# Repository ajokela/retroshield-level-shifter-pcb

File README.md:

# RetroShield Level Shifter PCB — Arduino Giga R1 Shield

KiCad design files for a bidirectional 3.3V-to-5V level converter shield that sits between an [Arduino Giga R1 WiFi](https://store.arduino.cc/products/giga-r1-wifi) and a [RetroShield Z80](https://www.tindie.com/products/8bitforce/retroshield-for-arduino-mega-z80/). The shield translates all bus signals between the Giga's 3.3V logic and the RetroShield's 5V logic.

## Design Overview

**Version:** V0.2

V0.1 used nine identical TXB0108PW auto-direction-sensing level translators. In practice, the TXB0108's direction sensing failed for several Z80 bus signals: `IORQ_N` and `RD_N` were stuck HIGH, the data bus was invisible during IO writes, and `WR_N` was unreliable during IO cycles. The firmware worked around these failures with ~1,300 lines of shadow register tracking code.

V0.2 replaces 5 of the 9 TXB0108s with purpose-matched ICs that have explicit direction control, eliminating these failures entirely:

| Position | IC | Package | Role |
|----------|---|---------|------|
| U1, U2, U3 | **SN74LVC541** | TSSOP-20 | Address bus + control inputs (5V→3.3V) |
| U4 | **SN74AHCT541** | TSSOP-20 | Control outputs (3.3V→5V) |
| U5 | **SN74LVC4245A** | TSSOP-24 | Data bus (bidirectional, explicit DIR) |
| U6–U9 | TXB0108PW | TSSOP-20 | Pass-through GPIO (unchanged) |

**Board specifications:**
- **Dimensions:** 155mm x 90mm (matches Arduino Giga R1 footprint)
- **Layers:** 2-layer PCB
- **Signals translated:** 72 channels covering data bus, address bus, and control signals
- **DIR pin:** Arduino D2 → U5 pin 2 (controls data bus direction)

### Signal Groups

| Signal Group | Pins | Channels | Direction | IC |
|-------------|------|----------|-----------|-----|
| Address bus A0–A7 | D22–D29 | 8 | Z80 → Arduino (5V→3.3V) | U1 (74LVC541) |
| Address bus A8–A15 | D30–D37 | 8 | Z80 → Arduino (5V→3.3V) | U2 (74LVC541) |
| Control (MREQ, IORQ, RD, WR) | D39–D41, D53 | 4 | Z80 → Arduino (5V→3.3V) | U3 (74LVC541) |
| Control (CLK, RESET, INT, NMI) | D38, D50–D52 | 4 | Arduino → Z80 (3.3V→5V) | U4 (74AHCT541) |
| Data bus D0–D7 | D42–D49 | 8 | Bidirectional (DIR pin) | U5 (SN74LVC4245A) |
| Remaining GPIO | Various | 40 | Bidirectional (auto-sense) | U6–U9 (TXB0108) |

### IC Selection Rationale

- **74LVC541** (U1–U3): VCC=3.3V, inputs are 5V-tolerant. Unidirectional buffer — no direction sensing ambiguity. OE pins tied to GND (always enabled). No pull-up resistors needed.
- **74AHCT541** (U4): VCC=5V, TTL-compatible inputs accept 3.3V drive levels. Unidirectional buffer for Arduino→Z80 control signals. OE pins tied to GND.
- **SN74LVC4245A** (U5): VCCA=3.3V, VCCB=5V. Bidirectional transceiver with explicit DIR pin. DIR HIGH = A→B (Giga drives Z80 data bus), DIR LOW = B→A (Z80 drives Giga). OE tied to GND. DIR pin connected directly to Arduino D2 at 3.3V (does not go through a level shifter).
- **TXB0108PW** (U6–U9): Retained for pass-through GPIO where auto-direction sensing works fine. OE pins pulled HIGH via 10K resistors to 3.3V.

### DIR Pin

The SN74LVC4245A (U5) requires one GPIO from the Giga for direction control:

- **Arduino pin D2** (directly connected at 3.3V, no level shifter)
- **DIR HIGH** → A→B: Giga drives Z80 data bus (memory/IO writes to Z80)
- **DIR LOW** → B→A: Z80 drives Giga data bus (memory/IO reads from Z80)

This single GPIO wire replaces the entire shadow register architecture from v0.1.

## Repository Contents

```
kicad/                  KiCad 8 source files
  ├── AlexJ_bz_ArduinoGigaShield.kicad_pro    Project file
  ├── AlexJ_bz_ArduinoGigaShield.kicad_sch    Schematic
  ├── AlexJ_bz_ArduinoGigaShield.kicad_pcb    PCB layout
  └── AlexJ_bz_ArduinoGigaShield.kicad_prl    Project preferences

gerber/                 Production-ready Gerber files (v0.1 — regenerate from KiCad for v0.2)
  ├── *-F_Cu.gbr           Front copper
  ├── *-B_Cu.gbr           Back copper
  ├── *-F_Mask.gbr         Front solder mask
  ├── *-B_Mask.gbr         Back solder mask
  ├── *-F_Silkscreen.gbr   Front silkscreen
  ├── *-B_Silkscreen.gbr   Back silkscreen
  ├── *-F_Paste.gbr        Front paste (for stencil)
  ├── *-B_Paste.gbr        Back paste
  ├── *-Edge_Cuts.gbr      Board outline
  ├── *-PTH.drl            Plated through-hole drill
  ├── *-NPTH.drl           Non-plated through-hole drill
  └── *-job.gbrjob         Gerber job file

bom/                    Bill of Materials
  ├── AlexJ_bz_ArduinoGigaShield.csv     CSV format
  └── AlexJ_bz_ArduinoGigaShield.xlsx    Excel format (v0.1)

cpl/                    Component Placement
  └── AlexJ_bz_ArduinoGigaShield-all-pos.csv   Pick & place positions

schematic/              Schematic PDF (v0.1 — regenerate from KiCad for v0.2)
  └── AlexJ_bz_ArduinoGigaShield.pdf

images/                 3D renders
  ├── AlexJ_bz_ArduinoGigaShield_TOP.jpg       Top view
  ├── AlexJ_bz_ArduinoGigaShield_TOP.png       Top view (PNG)
  ├── AlexJ_bz_ArduinoGigaShield_BTM.jpg       Bottom view
  └── AlexJ_bz_ArduinoGigaShield.png           Perspective view

CHANGES-V0.2.md         Detailed design changes for KiCad implementation
```

## Bill of Materials

| Reference | Qty | Value | Part Number | Package |
|-----------|-----|-------|-------------|---------|
| U1, U2, U3 | 3 | SN74LVC541 | SN74LVC541PWR | TSSOP-20 |
| U4 | 1 | SN74AHCT541 | SN74AHCT541PWR | TSSOP-20 |
| U5 | 1 | SN74LVC4245A | SN74LVC4245APWR | TSSOP-24 |
| U6–U9 | 4 | TXB0108PW | TXB0108PWR | TSSOP-20 |
| C1–C18 | 18 | 0.1 uF | CC0603KRX7R9BB104 | 0603 |
| R6–R9 | 4 | 10K | RC0603FR-0710KL | 0603 |

**Cap breakdown:** U1–U3 get 1 cap each (VCC only, single supply), U4 gets 1 cap (VCC only), U5 gets 2 caps (VCCA + VCCB), U6–U9 get 3 caps each (VCCA + VCCB + extra) = 3 + 1 + 2 + 12 = 18 caps.

**Resistors:** R6–R9 are 10K pull-ups on OE pins for U6–U9 (TXB0108). R1–R5 from v0.1 are removed — the 74LVC541, 74AHCT541, and SN74LVC4245A have their OE pins tied directly to GND.

## Manufacturing

The Gerber files in `gerber/` are from v0.1. After the KiCad schematic and PCB are updated for v0.2, regenerate Gerbers before ordering.

Upload to any PCB fabrication service:

- [PCBWay](https://www.pcbway.com/)
- [JLCPCB](https://jlcpcb.com/)
- [OSH Park](https://oshpark.com/)

For SMD assembly, provide the BOM (`bom/`) and component placement file (`cpl/`) to the fab house.

### Recommended PCB Specs

| Parameter | Value |
|-----------|-------|
| Layers | 2 |
| Board thickness | 1.6 mm |
| Copper weight | 1 oz |
| Surface finish | HASL or ENIG |
| Solder mask | Red (or your preference) |
| Silkscreen | White |

## Assembly Notes

1. **SMD components first** — solder the ICs, decoupling capacitors, and pull-up resistors
2. **Pin headers last** — solder the through-hole pin headers (female on bottom for the Giga, male on top for the RetroShield)
3. **Power jumper** — a jumper wire connects the Giga's 3.3V output to the shield's VCCA rail
4. **DIR wire** — connect Arduino D2 to U5 pin 2 (DIR) if not routed on the PCB
5. **Orientation** — check silkscreen for "V0.2" and IC labels; U5 is the wider TSSOP-24 package

## Photos

## Related Projects

- [retroshield-z80-cpm-giga](https://github.com/ajokela/retroshield-z80-cpm-giga) — Arduino Giga R1 firmware for CP/M 2.2 on the RetroShield Z80
- [retroshield-sector-server](https://github.com/ajokela/retroshield-sector-server) — Rust TCP server for WiFi-based CP/M disk I/O

## Blog Posts

This project is documented in a three-part series on [tinycomputers.io](https://tinycomputers.io):

1. [My Experience Using Fiverr for Custom PCB Design: A $468 Arduino Giga Shield](https://tinycomputers.io/posts/fiverr-pcb-design-arduino-giga-shield/)
2. [Porting CP/M to the Arduino Giga R1: When Level Converters Fight Back](https://tinycomputers.io/posts/cpm-on-arduino-giga-r1-wifi/)
3. [Playing Zork on a Real Z80: From CP/M Boot to the Great Underground Empire](https://tinycomputers.io/posts/zork-on-retroshield-z80-arduino-giga/)

## License

This work is licensed under the [Creative Commons Attribution-ShareAlike 4.0 International License](https://creativecommons.org/licenses/by-sa/4.0/) (CC BY-SA 4.0). See [LICENSE](LICENSE).

You are free to share and adapt this design, including for commercial purposes, as long as you give appropriate credit and distribute derivative works under the same license.

## Author

Alex Jokela — [tinycomputers.io](https://tinycomputers.io)

PCB design by Elijah (ekeziah) via Fiverr. Manufacturing sponsored by [PCBWay](https://www.pcbway.com/).

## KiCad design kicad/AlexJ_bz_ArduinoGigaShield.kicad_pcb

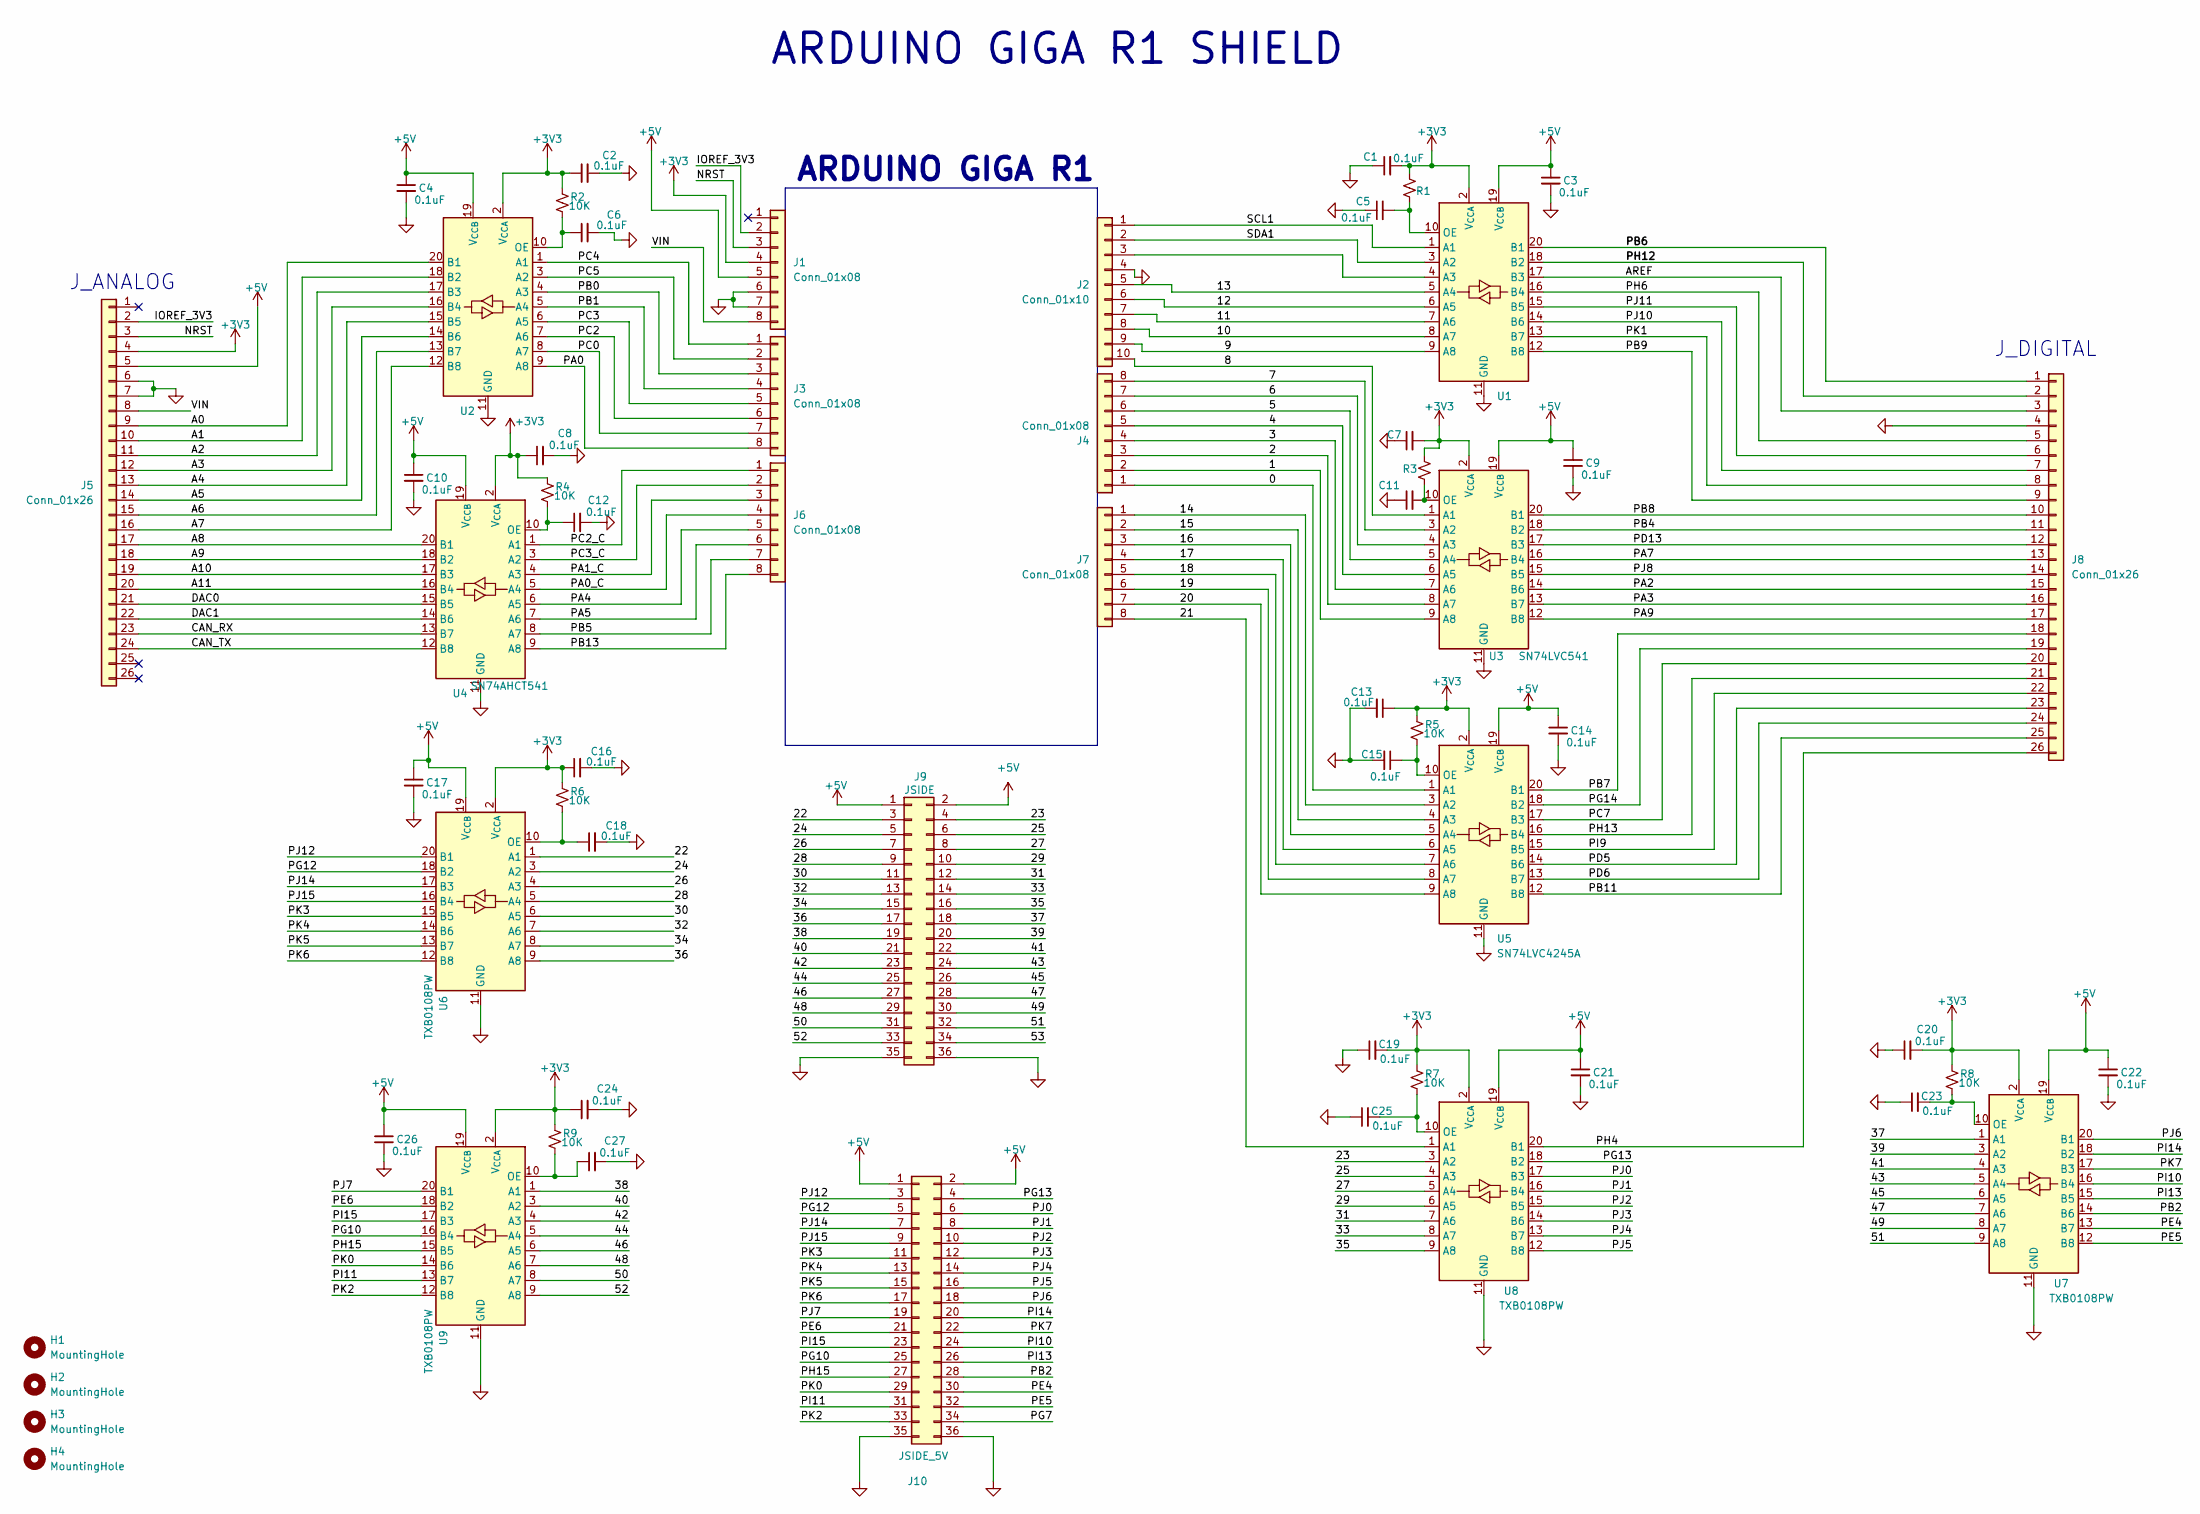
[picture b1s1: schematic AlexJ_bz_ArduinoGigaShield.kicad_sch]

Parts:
C1, C2, C3, C4, C5, C6, C7, C8, C9, C10, C11, C12, C13, C14, C15, C16, C17, C18, C19, C20, C21, C22, C23, C24, C25, C26, C27: 0.1uF; C_0603_1608Metric
H1, H2, H3, H4: MountingHole; MountingHole_3.2mm_M3
J1, J3, J4, J6, J7: Conn_01x08; PinHeader_1x08_P2.54mm_Vertical
J2: Conn_01x10; PinHeader_1x10_P2.54mm_Vertical
J5, J8: Conn_01x26; PinHeader_1x26_P2.54mm_Vertical
J9: JSIDE; PinHeader_2x18_P2.54mm_Vertical
J10: JSIDE_5V; PinHeader_2x18_P2.54mm_Vertical
R1, R2, R3, R4, R5, R6, R7, R8, R9: 10K; R_0603_1608Metric
U1, U2, U3: SN74LVC541; TSSOP-20_4.4x6.5mm_P0.65mm
U4: SN74AHCT541; TSSOP-20_4.4x6.5mm_P0.65mm
U5: SN74LVC4245A; TSSOP-24_4.4x7.8mm_P0.65mm
U6, U7, U8, U9: TXB0108PW; TSSOP-20_4.4x6.5mm_P0.65mm

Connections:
+3V3: C1.2, C2.1, C7.2, C8.1, C13.1, C16.1, C19.2, C20.2, C24.1, J1.4, J5.4, R1.1, R2.1, R3.1, R4.1, R5.1, R6.1, R7.1, R8.1, R9.1, U1.2 (V_{CCA}), U2.2 (V_{CCA}), U3.2 (V_{CCA}), U4.2 (V_{CCA}), U5.2 (V_{CCA}), U6.2 (V_{CCA}), U7.2 (V_{CCA}), U8.2 (V_{CCA}), U9.2 (V_{CCA})
+5V: C3.1, C4.1, C9.1, C10.1, C14.1, C17.1, C21.1, C22.1, C26.1, J1.5, J5.5, J9.1, J9.2, J10.1, J10.2, U1.19 (V_{CCB}), U2.19 (V_{CCB}), U3.19 (V_{CCB}), U4.19 (V_{CCB}), U5.19 (V_{CCB}), U6.19 (V_{CCB}), U7.19 (V_{CCB}), U8.19 (V_{CCB}), U9.19 (V_{CCB})
/0: J4.1, U5.1 (A1)
/1: J4.2, U3.9 (A8)
/2: J4.3, U3.8 (A7)
/3: J4.4, U3.7 (A6)
/4: J4.5, U3.6 (A5)
/5: J4.6, U3.5 (A4)
/6: J4.7, U3.4 (A3)
/7: J4.8, U3.3 (A2)
/8: J2.10, U3.1 (A1)
/9: J2.9, U1.9 (A8)
/10: J2.8, U1.8 (A7)
/11: J2.7, U1.7 (A6)
/12: J2.6, U1.6 (A5)
/13: J2.5, U1.5 (A4)
/14: J7.1, U5.3 (A2)
/15: J7.2, U5.4 (A3)
/16: J7.3, U5.5 (A4)
/17: J7.4, U5.6 (A5)
/18: J7.5, U5.7 (A6)
/19: J7.6, U5.8 (A7)
/20: J7.7, U5.9 (A8)
/21: J7.8, U8.1 (A1)
/22: J9.3, U6.1 (A1)
/23: J9.4, U8.3 (A2)
/24: J9.5, U6.3 (A2)
/25: J9.6, U8.4 (A3)
/26: J9.7, U6.4 (A3)
/27: J9.8, U8.5 (A4)
/28: J9.9, U6.5 (A4)
/29: J9.10, U8.6 (A5)
/30: J9.11, U6.6 (A5)
/31: J9.12, U8.7 (A6)
/32: J9.13, U6.7 (A6)
/33: J9.14, U8.8 (A7)
/34: J9.15, U6.8 (A7)
/35: J9.16, U8.9 (A8)
/36: J9.17, U6.9 (A8)
/37: J9.18, U7.1 (A1)
/38: J9.19, U9.1 (A1)
/39: J9.20, U7.3 (A2)
/40: J9.21, U9.3 (A2)
/41: J9.22, U7.4 (A3)
/42: J9.23, U9.4 (A3)
/43: J9.24, U7.5 (A4)
/44: J9.25, U9.5 (A4)
/45: J9.26, U7.6 (A5)
/46: J9.27, U9.6 (A5)
/47: J9.28, U7.7 (A6)
/48: J9.29, U9.7 (A6)
/49: J9.30, U7.8 (A7)
/50: J9.31, U9.8 (A7)
/51: J9.32, U7.9 (A8)
/52: J9.33, U9.9 (A8)
/53: J9.34
/A0: J5.9, U2.20 (B1)
/A1: J5.10, U2.18 (B2)
/A2: J5.11, U2.17 (B3)
/A3: J5.12, U2.16 (B4)
/A4: J5.13, U2.15 (B5)
/A5: J5.14, U2.14 (B6)
/A6: J5.15, U2.13 (B7)
/A7: J5.16, U2.12 (B8)
/A8: J5.17, U4.20 (B1)
/A9: J5.18, U4.18 (B2)
/A10: J5.19, U4.17 (B3)
/A11: J5.20, U4.16 (B4)
/AREF: J8.3, U1.17 (B3)
/CAN_RX: J5.23, U4.13 (B7)
/CAN_TX: J5.24, U4.12 (B8)
/DAC0: J5.21, U4.15 (B5)
/DAC1: J5.22, U4.14 (B6)
/IOREF_3V3: J1.2, J5.2
/NRST: J1.3, J5.3
/PA0: J3.8, U2.9 (A8)
/PA0_C: J6.4, U4.5 (A4)
/PA1_C: J6.3, U4.4 (A3)
/PA2: J8.15, U3.14 (B6)
/PA3: J8.16, U3.13 (B7)
/PA4: J6.5, U4.6 (A5)
/PA5: J6.6, U4.7 (A6)
/PA7: J8.13, U3.16 (B4)
/PA9: J8.17, U3.12 (B8)
/PB0: J3.3, U2.4 (A3)
/PB1: J3.4, U2.5 (A4)
/PB2: J10.28, U7.14 (B6)
/PB4: J8.11, U3.18 (B2)
/PB5: J6.7, U4.8 (A7)
/PB6: J8.1, U1.20 (B1)
/PB7: J8.18, U5.20 (B1)
/PB8: J8.10, U3.20 (B1)
/PB9: J8.9, U1.12 (B8)
/PB11: J8.25, U5.12 (B8)
/PB13: J6.8, U4.9 (A8)
/PC0: J3.7, U2.8 (A7)
/PC2: J3.6, U2.7 (A6)
/PC2_C: J6.1, U4.1 (A1)
/PC3: J3.5, U2.6 (A5)
/PC3_C: J6.2, U4.3 (A2)
/PC4: J3.1, U2.1 (A1)
/PC5: J3.2, U2.3 (A2)
/PC7: J8.20, U5.17 (B3)
/PD5: J8.23, U5.14 (B6)
/PD6: J8.24, U5.13 (B7)
/PD13: J8.12, U3.17 (B3)
/PE4: J10.30, U7.13 (B7)
/PE5: J10.32, U7.12 (B8)
/PE6: J10.21, U9.18 (B2)
/PG7: J10.34
/PG10: J10.25, U9.16 (B4)
/PG12: J10.5, U6.18 (B2)
/PG13: J10.4, U8.18 (B2)
/PG14: J8.19, U5.18 (B2)
/PH4: J8.26, U8.20 (B1)
/PH6: J8.5, U1.16 (B4)
/PH12: J8.2, U1.18 (B2)
/PH13: J8.21, U5.16 (B4)
/PH15: J10.27, U9.15 (B5)
/PI9: J8.22, U5.15 (B5)
/PI10: J10.24, U7.16 (B4)
/PI11: J10.31, U9.13 (B7)
/PI13: J10.26, U7.15 (B5)
/PI14: J10.20, U7.18 (B2)
/PI15: J10.23, U9.17 (B3)
/PJ0: J10.6, U8.17 (B3)
/PJ1: J10.8, U8.16 (B4)
/PJ2: J10.10, U8.15 (B5)
/PJ3: J10.12, U8.14 (B6)
/PJ4: J10.14, U8.13 (B7)
/PJ5: J10.16, U8.12 (B8)
/PJ6: J10.18, U7.20 (B1)
/PJ7: J10.19, U9.20 (B1)
/PJ8: J8.14, U3.15 (B5)
/PJ10: J8.7, U1.14 (B6)
/PJ11: J8.6, U1.15 (B5)
/PJ12: J10.3, U6.20 (B1)
/PJ14: J10.7, U6.17 (B3)
/PJ15: J10.9, U6.16 (B4)
/PK0: J10.29, U9.14 (B6)
/PK1: J8.8, U1.13 (B7)
/PK2: J10.33, U9.12 (B8)
/PK3: J10.11, U6.15 (B5)
/PK4: J10.13, U6.14 (B6)
/PK5: J10.15, U6.13 (B7)
/PK6: J10.17, U6.12 (B8)
/PK7: J10.22, U7.17 (B3)
/SCL1: J2.1, U1.1 (A1)
/SDA1: J2.2, U1.3 (A2)
/VIN: J1.8, J5.8
GND: C1.1, C2.2, C3.2, C4.2, C5.1, C6.2, C7.1, C8.2, C9.2, C10.2, C11.1, C12.2, C13.2, C14.2, C15.2, C16.2, C17.2, C18.2, C19.1, C20.1, C21.2, C22.2, C23.1, C24.2, C25.1, C26.2, C27.2, J1.6, J1.7, J2.4, J5.6, J5.7, J8.4, J9.35, J9.36, J10.35, J10.36, U1.11 (GND), U2.11 (GND), U3.11 (GND), U4.11 (GND), U5.11 (GND), U6.11 (GND), U7.11 (GND), U8.11 (GND), U9.11 (GND)
unnamed: J2.3, U1.4 (A3)
unnamed: C5.2, R1.2, U1.10 (OE)
unnamed: C6.1, R2.2, U2.10 (OE)
unnamed: C11.2, R3.2, U3.10 (OE)
unnamed: C12.1, R4.2, U4.10 (OE)
unnamed: C15.1, R5.2, U5.10 (OE)
unnamed: C18.1, R6.2, U6.10 (OE)
unnamed: C23.2, R8.2, U7.10 (OE)
unnamed: C25.2, R7.2, U8.10 (OE)
unnamed: C27.1, R9.2, U9.10 (OE)

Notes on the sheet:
J_ANALOG
ARDUINO GIGA R1 SHIELD
J_DIGITAL
ARDUINO GIGA R1

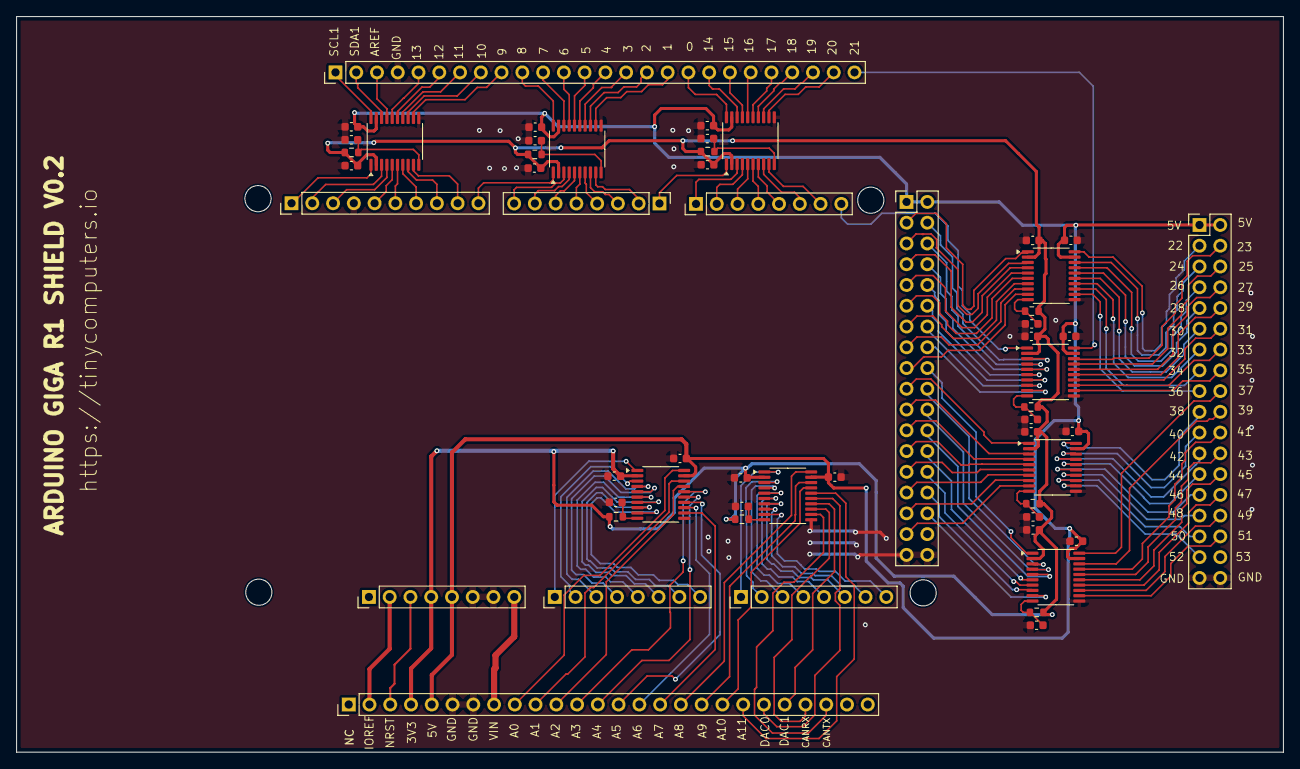
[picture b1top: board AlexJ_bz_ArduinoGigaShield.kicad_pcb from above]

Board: 2 copper layers, 155.0 x 90.0 mm, 59 parts (0 on the bottom side), 159 nets.

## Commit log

2026-02-15 Initial release: KiCad design files for Arduino Giga R1 level converter shield
2026-02-15 v0.2 design: replace 5x TXB0108 with purpose-matched level translators
    Replace U1-U3 with SN74LVC541 (address bus, control inputs),
    U4 with SN74AHCT541 (control outputs), and U5 with SN74LVC4245A
    (data bus with explicit DIR pin). Eliminates TXB0108 auto-direction
    sensing failures on IORQ_N, RD_N, and data bus during IO writes.
    Updated BOM, CPL, README, and added CHANGES-V0.2.md with detailed
    KiCad schematic/PCB implementation guide for the designer.
2026-02-15 Update KiCad schematic and PCB annotations for v0.2 IC replacements
    Schematic: Update Value, Datasheet, and Description properties on U1-U5
    to reflect new IC types (SN74LVC541, SN74AHCT541, SN74LVC4245A).
    Update U5 Footprint property to TSSOP-24.
    PCB: Update Value, Datasheet, and Description on U1-U5 footprints.
    Update U5 footprint reference to TSSOP-24. Change silkscreen from
    V0.1 to V0.2.
2026-02-15 v0.2 schematic: replace U1-U5 with purpose-matched level translators
    - Replace U1-U3 lib_symbols from TXB0108PW to SN74LVC541 (address bus + control inputs)
    - Replace U4 lib_symbol to SN74AHCT541 (control outputs)
    - Replace U5 lib_symbol to SN74LVC4245A (bidirectional data bus with DIR)
    - Add lib_symbol definitions for SN74LVC541, SN74AHCT541, SN74LVC4245A
    - Remove R1-R5 pull-up resistors (OE pins now tied to GND)
    - Add GND symbols at 1OE and 2OE pins for U1-U4
2026-02-15 Remove C19-C27 extra decoupling caps from schematic
    The v0.1 design had 27 caps (3 per TXB0108). With v0.2's single-supply
    ICs (U1-U4), only 1 cap per IC is needed. U5 keeps 2 (VCCA+VCCB).
    U6-U9 keep 3 each. Total: 18 caps (C1-C18).
    Also removes 7 dedicated GND symbols and connecting wires.
2026-02-15 Add DATA_DIR net, U5 hidden GND pins, and update change log
    - Add DATA_DIR label at U5 DIR pin (262.89, 148.59)
    - Add DATA_DIR label on Arduino D2 wire (225.0, 93.98) to connect nets
    - Add hidden GND pins 7, 17, 22 to SN74LVC4245A lib_symbol
    - Update CHANGES-V0.2.md with completed schematic edits and remaining GUI work
